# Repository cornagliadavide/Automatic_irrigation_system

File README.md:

# Automatic Irrigation System

Questo è un progetto basato su Arduino per gestire l'irrigazione automatica delle piante. 
Il sistema monitora costantemente l'umidità del terreno e attiva automaticamente una pompa per l'irrigazione quando necessario, evitando che le piante si secchino.

## Componenti Hardware

### Logica e Controllo
* **Arduino Nano** (ATmega328P) — microcontrollore principale
* **Modulo driver MOSFET dual-channel** — pilota la pompa ad alta corrente tramite segnale PWM (Pin D9)
* **Modulo Bluetooth HC-05** — per il monitoraggio/controllo remoto tramite comunicazione seriale (38400 baud)
### Sensori
* **Sensore di umidità del suolo capacitivo** — collegato al pin A0
* **Sensore di livello a galleggiante** — collegato al pin A2
* **Partitore di tensione** (R₁ = 10 kΩ, R₂ = 4.7 kΩ) — per la lettura della tensione della batteria sul pin A4

### Alimentazione ed Energia
* **2× Pannelli solari** da 6V. 3W — collegati in serie (12V)
* **2× Celle Li-Ion 18650**
* **Pacco batterie di riserva** — 4× stilo AA (6V)
* **Modulo di ricarica TP5100** — ricarica in due fasi (corrente/tensione costante), configurato per 2 celle in serie (8.4V)
* **BMS 2S** — protezione da sovraccarica e scarica profonda - Corrente massima di 3A
* **Convertitore Buck XL4015** — step-down regolabile, stabilizza l'uscita a 5V
* **Condensatore** da 2200µF 25V — bypass anti-spunto in parallelo alla pompa

### Attuazione
* **Pompa dell'acqua a immersione** 5V
* **Diodi di protezione**: 1N5822 Schottky (linea solare) + 1N4007 (linea di riserva)

### Struttura e Prototipazione
* **Basetta millefori** (per il montaggio definitivo)
* **Contenitore stampato in 3D** con supporto per i pannelli solari
##  Debugging & Note Operative

Durante la fase di prototipazione e test sono stati individuati e risolti i seguenti punti critici per la stabilità del sistema:

1. **Gestione dello Spunto Meccanico ed Elettrico:**
   * La pompa richiede una corrente di spunto elevata per vincere l'inerzia iniziale della girante.
   * È stato configurato un impulso PWM al valore massimo (`255`) per una durata continua di **5 secondi** per garantire il corretto spunto e l'erogazione costante.
   * L'aggiunta del condensatore previene crolli di tensione improvvisi sulla logica dell'Arduino Nano durante la commutazione del MOSFET.
     
2. **Cablaggio e Connessioni di Potenza:**
   * **Morsetti a vite del MOSFET:** Evitare l'uso di pin rigidi flessibili o guaine termorestringenti all'interno dei morsetti a vite blu del MOSFET. Per garantire il passaggio delle correnti di picco senza cadute di tensione resistive, i fili multifilo della pompa vanno spellati e serrati a **rame nudo** direttamente nei morsetti.
   * **Manutenzione Girante:** In caso di mancato avvio con segnale PWM presente, verificare lo sblocco meccanico manuale della girante da eventuali sedimenti o attriti interni.
     
3. **Isolamento della Linea di Potenza:**
   * L'alimentazione USB del PC alimenta unicamente la logica del microcontrollore e i sensori. Per l'attivazione della pompa è sempre necessaria la presenza della linea di potenza attiva (batterie/Buck converter).

##  Struttura del Progetto
* `arduino_code/`: Contiene lo sketch (.ino) da caricare sulla scheda Arduino.
* `schematic/`: Contiene gli schemi elettrici per collegare correttamente i pin.

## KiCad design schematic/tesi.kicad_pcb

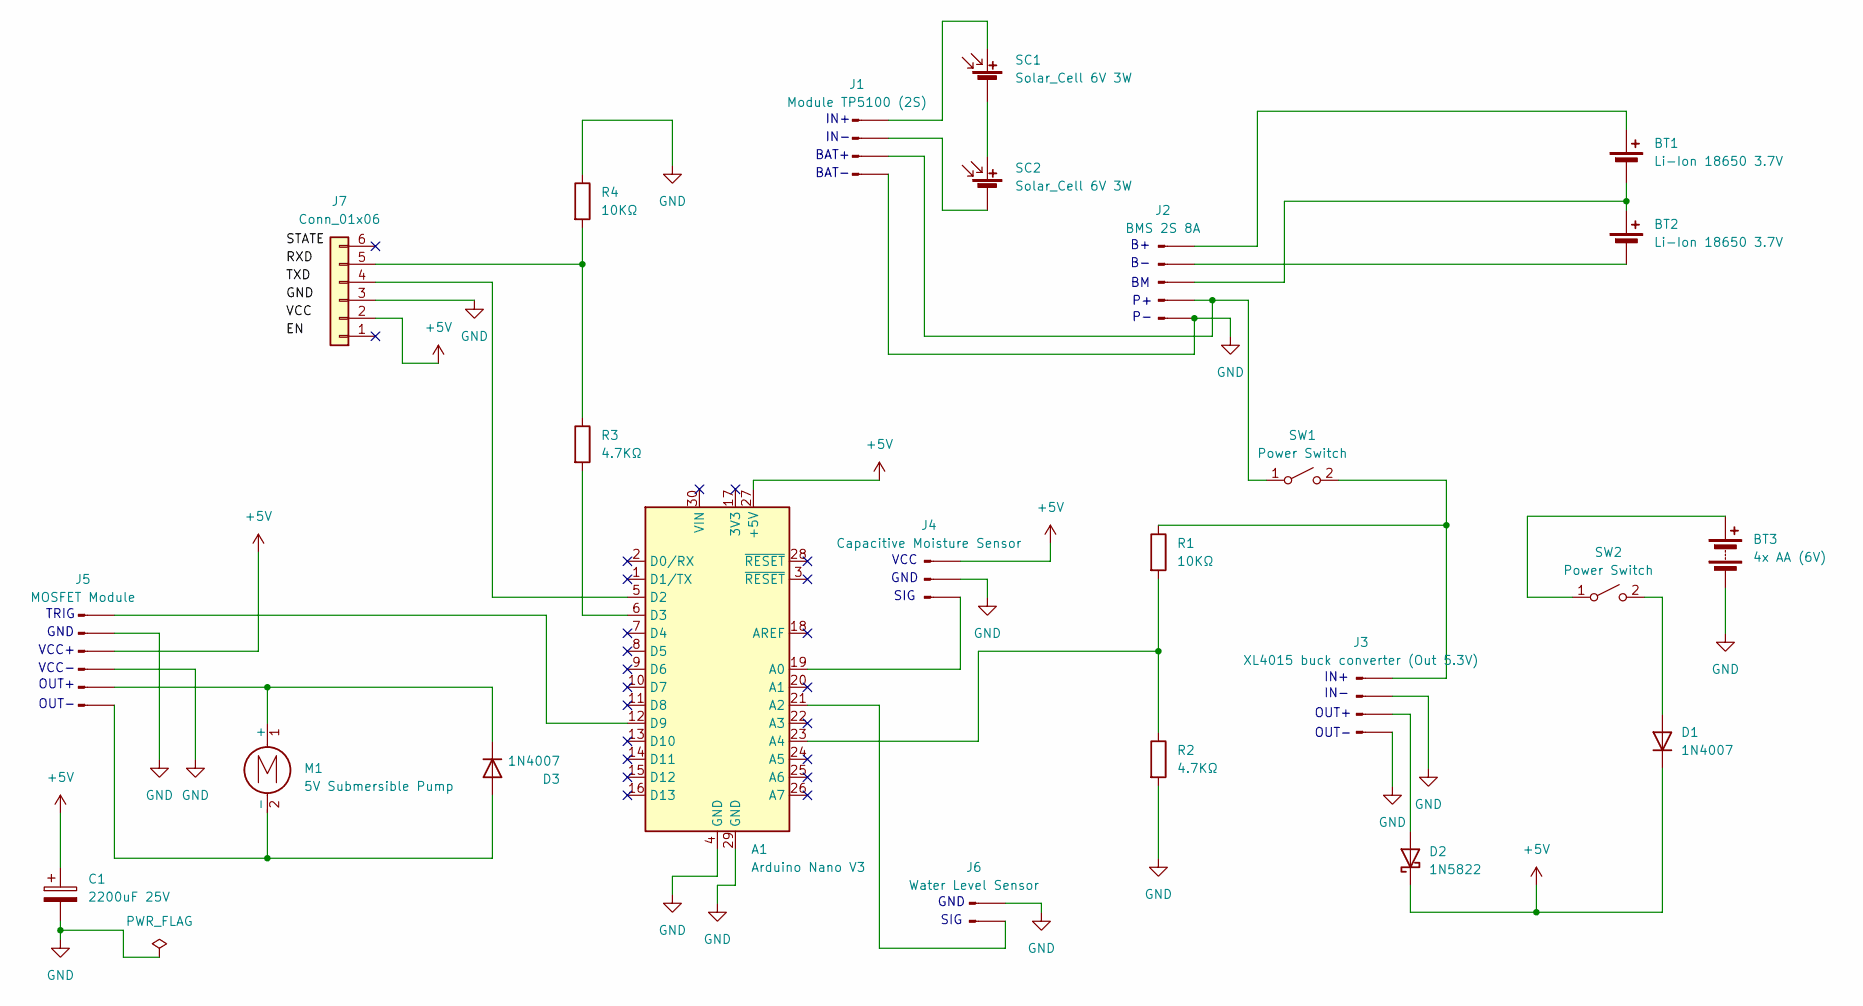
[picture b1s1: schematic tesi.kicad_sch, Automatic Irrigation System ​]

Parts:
A1: Arduino Nano V3; Arduino_Nano_WithMountingHoles
BT1, BT2: Li-Ion 18650 3.7V; TerminalBlock_Phoenix_MKDS-1,5-2_1x02_P5.00mm_Horizontal
BT3: 4x AA (6V); TerminalBlock_Phoenix_MKDS-1,5-2_1x02_P5.00mm_Horizontal
C1: 2200uF 25V; CP_Radial_D10.0mm_P5.00mm
D1, D3: 1N4007; D_DO-41_SOD81_P10.16mm_Horizontal
D2: 1N5822; D_DO-41_SOD81_P10.16mm_Horizontal
J1: Module TP5100 (2S); PinSocket_1x04_P2.54mm_Vertical
J2: BMS 2S 8A; PinSocket_1x05_P2.54mm_Vertical
J3: XL4015 buck converter (Out 5.3V); PinSocket_1x04_P2.54mm_Vertical
J4: Capacitive Moisture Sensor; PinSocket_1x03_P2.54mm_Vertical
J5: MOSFET Module; PinSocket_1x06_P2.54mm_Vertical
J6: Water Level Sensor; PinSocket_1x02_P2.54mm_Vertical
J7: Conn_01x06; PinHeader_1x06_P2.54mm_Vertical
M1: 5V Submersible Pump; TerminalBlock_Phoenix_MKDS-1,5-2-5.08_1x02_P5.08mm_Horizont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
R1, R4: 10KΩ; R_Axial_DIN0207_L6.3mm_D2.5mm_P10.16mm_Horizontal
R2, R3: 4.7KΩ; R_Axial_DIN0207_L6.3mm_D2.5mm_P10.16mm_Horizontal
SC1, SC2: Solar_Cell 6V 3W; TerminalBlock_Phoenix_MKDS-1,5-2-5.08_1x02_P5.08mm_Horizont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
SW1, SW2: Power Switch; TerminalBlock_Phoenix_MKDS-1,5-2_1x02_P5.00mm_Horizontal

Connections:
+5V: A1.27 (+5V), C1.1, D1.1 (K), D2.1 (K), J4.1, J5.3, J7.2
GND: A1.4 (GND), A1.29 (GND), BT3.2 (-), C1.2, J1.4, J2.5, J3.2, J3.4, J4.2, J5.2, J5.4, J6.1, J7.3, R2.2, R4.1
unnamed: A1.19 (A0), J4.3
unnamed: A1.21 (A2), J6.2
unnamed: A1.23 (A4), R1.2, R2.1
unnamed: A1.5 (D2), J7.4
unnamed: A1.6 (D3), R3.2
unnamed: A1.12 (D9), J5.1
unnamed: BT1.1 (+), J2.1
unnamed: BT1.2 (-), BT2.1 (+), J2.3
unnamed: BT2.2 (-), J2.2
unnamed: BT3.1 (+), SW2.1 (A)
unnamed: D1.2 (A), SW2.2 (B)
unnamed: D2.2 (A), J3.3
unnamed: D3.2 (A), J5.6, M1.2 (-)
unnamed: D3.1 (K), J5.5, M1.1 (+)
unnamed: J1.1, SC1.1 (+)
unnamed: J1.2, SC2.2 (-)
unnamed: J1.3, J2.4, SW1.1 (A)
unnamed: J3.1, R1.1, SW1.2 (B)
unnamed: J7.5, R3.1, R4.2
unnamed: SC1.2 (-), SC2.1 (+)

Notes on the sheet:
OUT+
IN+
TRIG
VCC-
BAT-
BAT+
IN-
OUT-
GND
VCC+
VCC
SIG

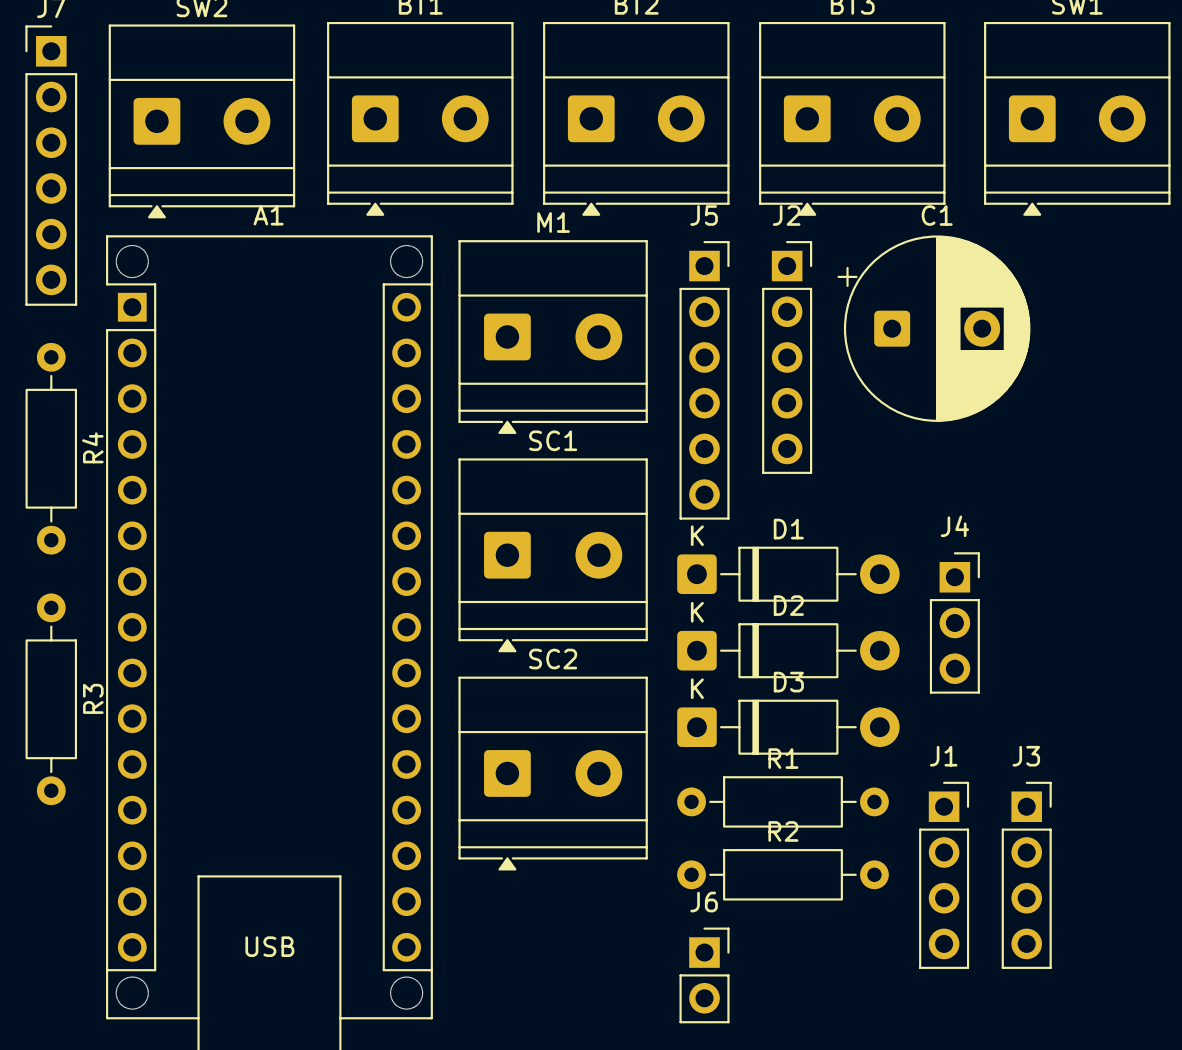
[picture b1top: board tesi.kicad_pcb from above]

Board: 2 copper layers, 24 parts (0 on the bottom side), 22 nets.
